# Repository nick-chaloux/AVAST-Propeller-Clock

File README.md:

# AVAST-Propeller-Clock
A Lunch &amp; Learn series where we will learn electronic assembly and soldering skills while building an actual product from idea to finished assembly.

## Lunch &amp; Learn Details
Instructor and email: Brian Kelly - avast-tech@whoi.edu\
Office: AVAST 108 - 508-289-3921\
Office Hours: 9 to 5, Monday through Friday\
Meeting Day and Time: Wednesdays from 11 to 1\
Location: David Center Social hub

**Schedule\***
* 3/5&nbsp;&nbsp;&nbsp;&nbsp;-- Project kickoff - overview of project and setup of free software
* 3/19&nbsp;&nbsp;--
* 3/26&nbsp;&nbsp;--

\* Schedule subject to some change. In-class time is intended for questions as you build your propeller clock

## How to Download this Repo
1. Install [git](https://git-scm.com/book/en/v2/Getting-Started-Installing-Git) on your local machine.
2. Navigate to the directory (folder) you want this project to download to.
3. Run:
```
git clone https://github.com/nick-chaloux/AVAST-Propeller-Clock.git
```

## Free Software!
All software is available for Window, macOS and Linux.

Mechanical: [Shapr3D](https://www.shapr3d.com/product/3d-modeling)
- Create a free account using your WHOI credentials

Electrical: [KiCAD](https://www.kicad.org/download/)

Software: [Arduino IDE](https://www.arduino.cc/en/software)

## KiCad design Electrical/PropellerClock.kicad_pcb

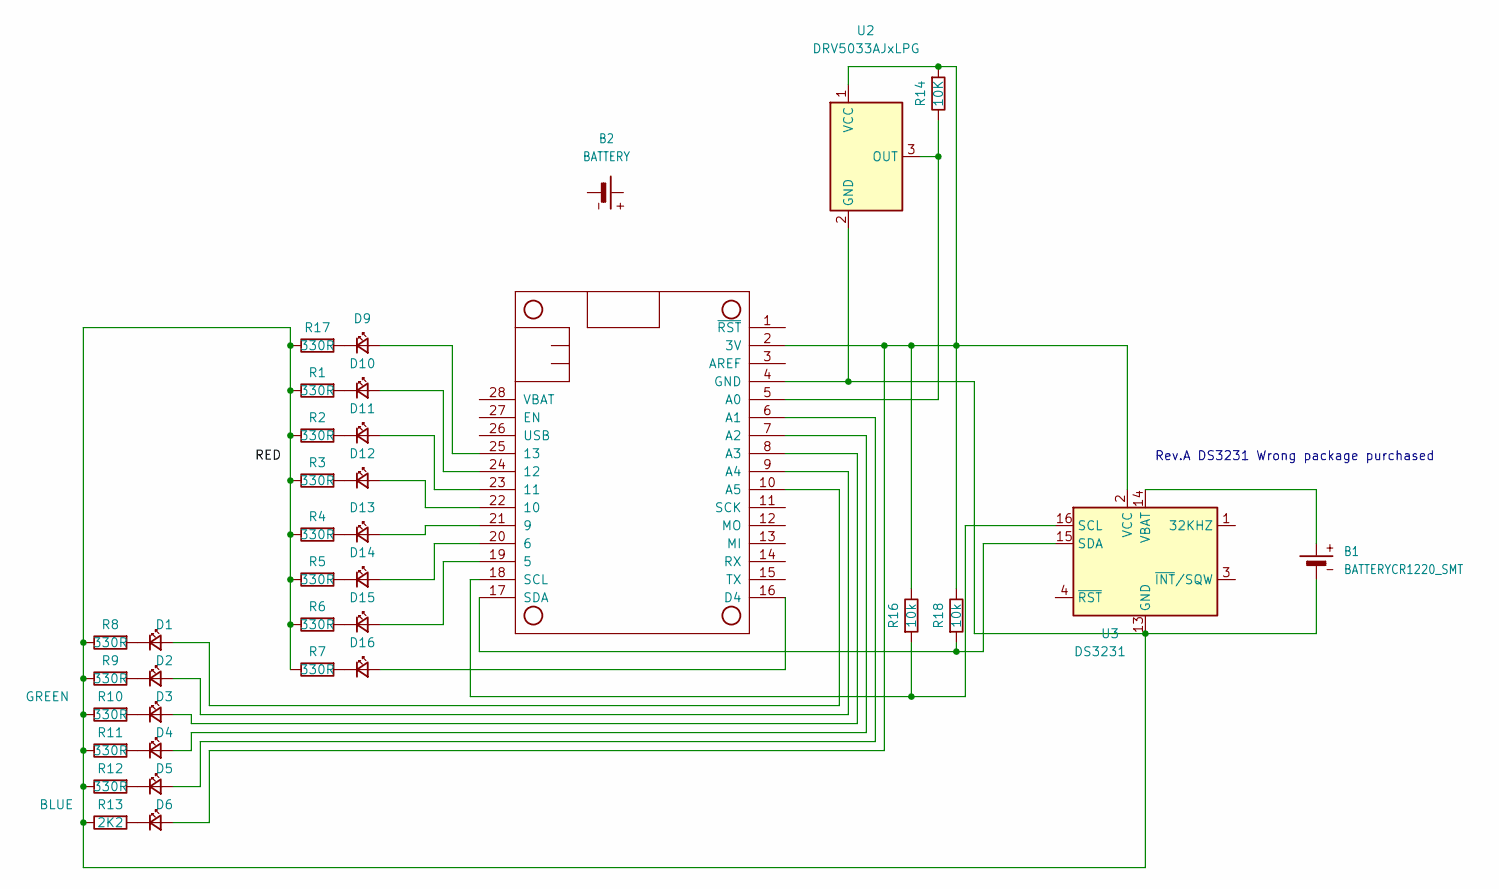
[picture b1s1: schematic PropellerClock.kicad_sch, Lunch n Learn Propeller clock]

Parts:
B1: BATTERYCR1220_SMT; BAT_CR-1220_FCN; Digikey P279-ND
B2: BATTERY; JSTPH2; Digikey 1528-1841-ND
D1, D2, D3, D4: LED_Small; LED_1206_3216Metric_Pad1.42x1.75mm_HandSolder; Digikey 1080-1419-1-ND
D5: GREEN; LED_1206_3216Metric_Pad1.42x1.75mm_HandSolder; Digikey 1080-1419-1-ND
D6: BLUE; LED_1206_3216Metric_Pad1.42x1.75mm_HandSolder; Digikey 1497-1399-1-ND
D9, D10, D11, D12, D13, D14, D15, D16: LED_Small; LED_1206_3216Metric_Pad1.42x1.75mm_HandSolder; Digikey L62301CT-ND
MS1: FEATHERWING; MODULE_FEATHER_M0_BASIC_PROTO; Digikey 1528-2538-ND
R1, R2, R3, R4, R5, R6, R7, R8, R9, R10, R11, R12, R17: 330R; R_Axial_DIN0207_L6.3mm_D2.5mm_P10.16mm_Horizontal; Digikey CF14JT330R
R13: 2K2; R_Axial_DIN0207_L6.3mm_D2.5mm_P10.16mm_Horizontal; Digikey CF14JT2K20
R14: 10K; R_Axial_DIN0207_L6.3mm_D2.5mm_P10.16mm_Horizontal; Digikey CF14JT10K0
R16, R18: 10k; R_Axial_DIN0207_L6.3mm_D2.5mm_P10.16mm_Horizontal; Digikey CF14JT10K0
U2: DRV5033AJxLPG; TO-92_Inline; Digikey 296-DRV5033AJQLPGMCT-ND
U3: DS3231; SO-16_5.3x10.2mm_P1.27mm; Digikey DS3231M+TRLCT-ND

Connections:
unnamed: D1.2 (A), MS1.10 (A5)
unnamed: D1.1 (K), R8.1
unnamed: D2.2 (A), MS1.9 (A4)
unnamed: D2.1 (K), R9.1
unnamed: D3.2 (A), MS1.8 (A3)
unnamed: D3.1 (K), R10.1
unnamed: D4.2 (A), MS1.7 (A2)
unnamed: D4.1 (K), R11.1
unnamed: D5.2 (A), MS1.6 (A1)
unnamed: D5.1 (K), R12.1
unnamed: D6.2 (A), MS1.2 (3V), R14.1, R16.2, R18.2, U2.1 (VCC), U3.2 (VCC)
unnamed: D6.1 (K), R13.1
unnamed: D9.2 (A), MS1.25 (13)
unnamed: D9.1 (K), R17.1
unnamed: D10.2 (A), MS1.24 (12)
unnamed: D10.1 (K), R1.1
unnamed: D11.2 (A), MS1.23 (11)
unnamed: D11.1 (K), R2.1
unnamed: D12.2 (A), MS1.22 (10)
unnamed: D12.1 (K), R3.1
unnamed: D13.2 (A), MS1.21 (9)
unnamed: D13.1 (K), R4.1
unnamed: D14.2 (A), MS1.20 (6)
unnamed: D14.1 (K), R5.1
unnamed: D15.2 (A), MS1.19 (5)
unnamed: D15.1 (K), R6.1
unnamed: D16.2 (A), MS1.16 (D4)
unnamed: D16.1 (K), R7.1
unnamed: MS1.5 (A0), R14.2, U2.3 (OUT)
unnamed: B1.-, MS1.4 (GND), R1.2, R2.2, R3.2, R4.2, R5.2, R6.2, R7.2, R8.2, R9.2, R10.2, R11.2, R12.2, R13.2, R17.2, U2.2 (GND), U3.5 (GND), U3.6 (GND), U3.7 (GND), U3.8 (GND), U3.9 (GND), U3.10 (GND), U3.11 (GND), U3.12 (GND), U3.13 (GND)
unnamed: MS1.18 (SCL), R16.1, U3.16 (SCL)
unnamed: MS1.17 (SDA), R18.1, U3.15 (SDA)
unnamed: B1.+, U3.14 (VBAT)

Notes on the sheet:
Rev.A DS3231 Wrong package purchased

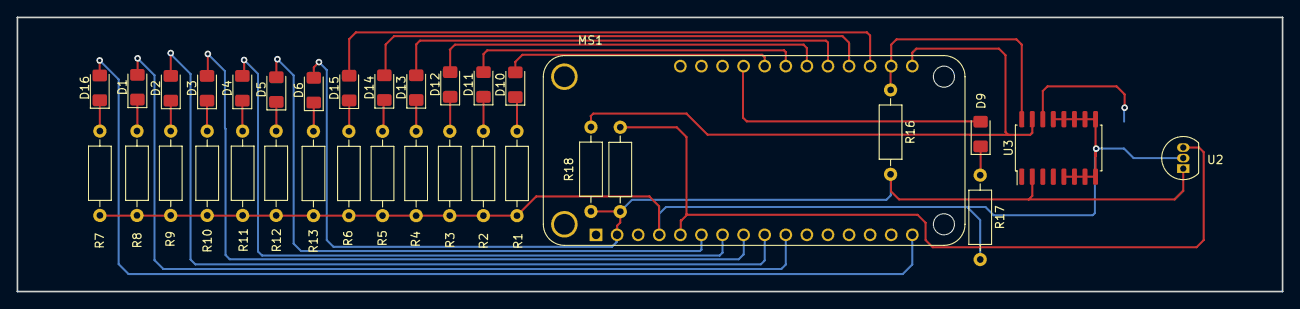
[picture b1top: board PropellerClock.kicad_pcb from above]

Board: 2 copper layers, 152.4 x 33.0 mm, 35 parts (1 on the bottom side), 33 nets.

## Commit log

2025-03-04 Update LICENSE
2025-03-05 Initial commit of Brian Kelleys work
2025-03-24 Added 3D models used on PCB
2025-05-12 Added pin names SVG, link to RTC instructions, and LEDS test code
2025-05-12 Added more links to RTC instructions
